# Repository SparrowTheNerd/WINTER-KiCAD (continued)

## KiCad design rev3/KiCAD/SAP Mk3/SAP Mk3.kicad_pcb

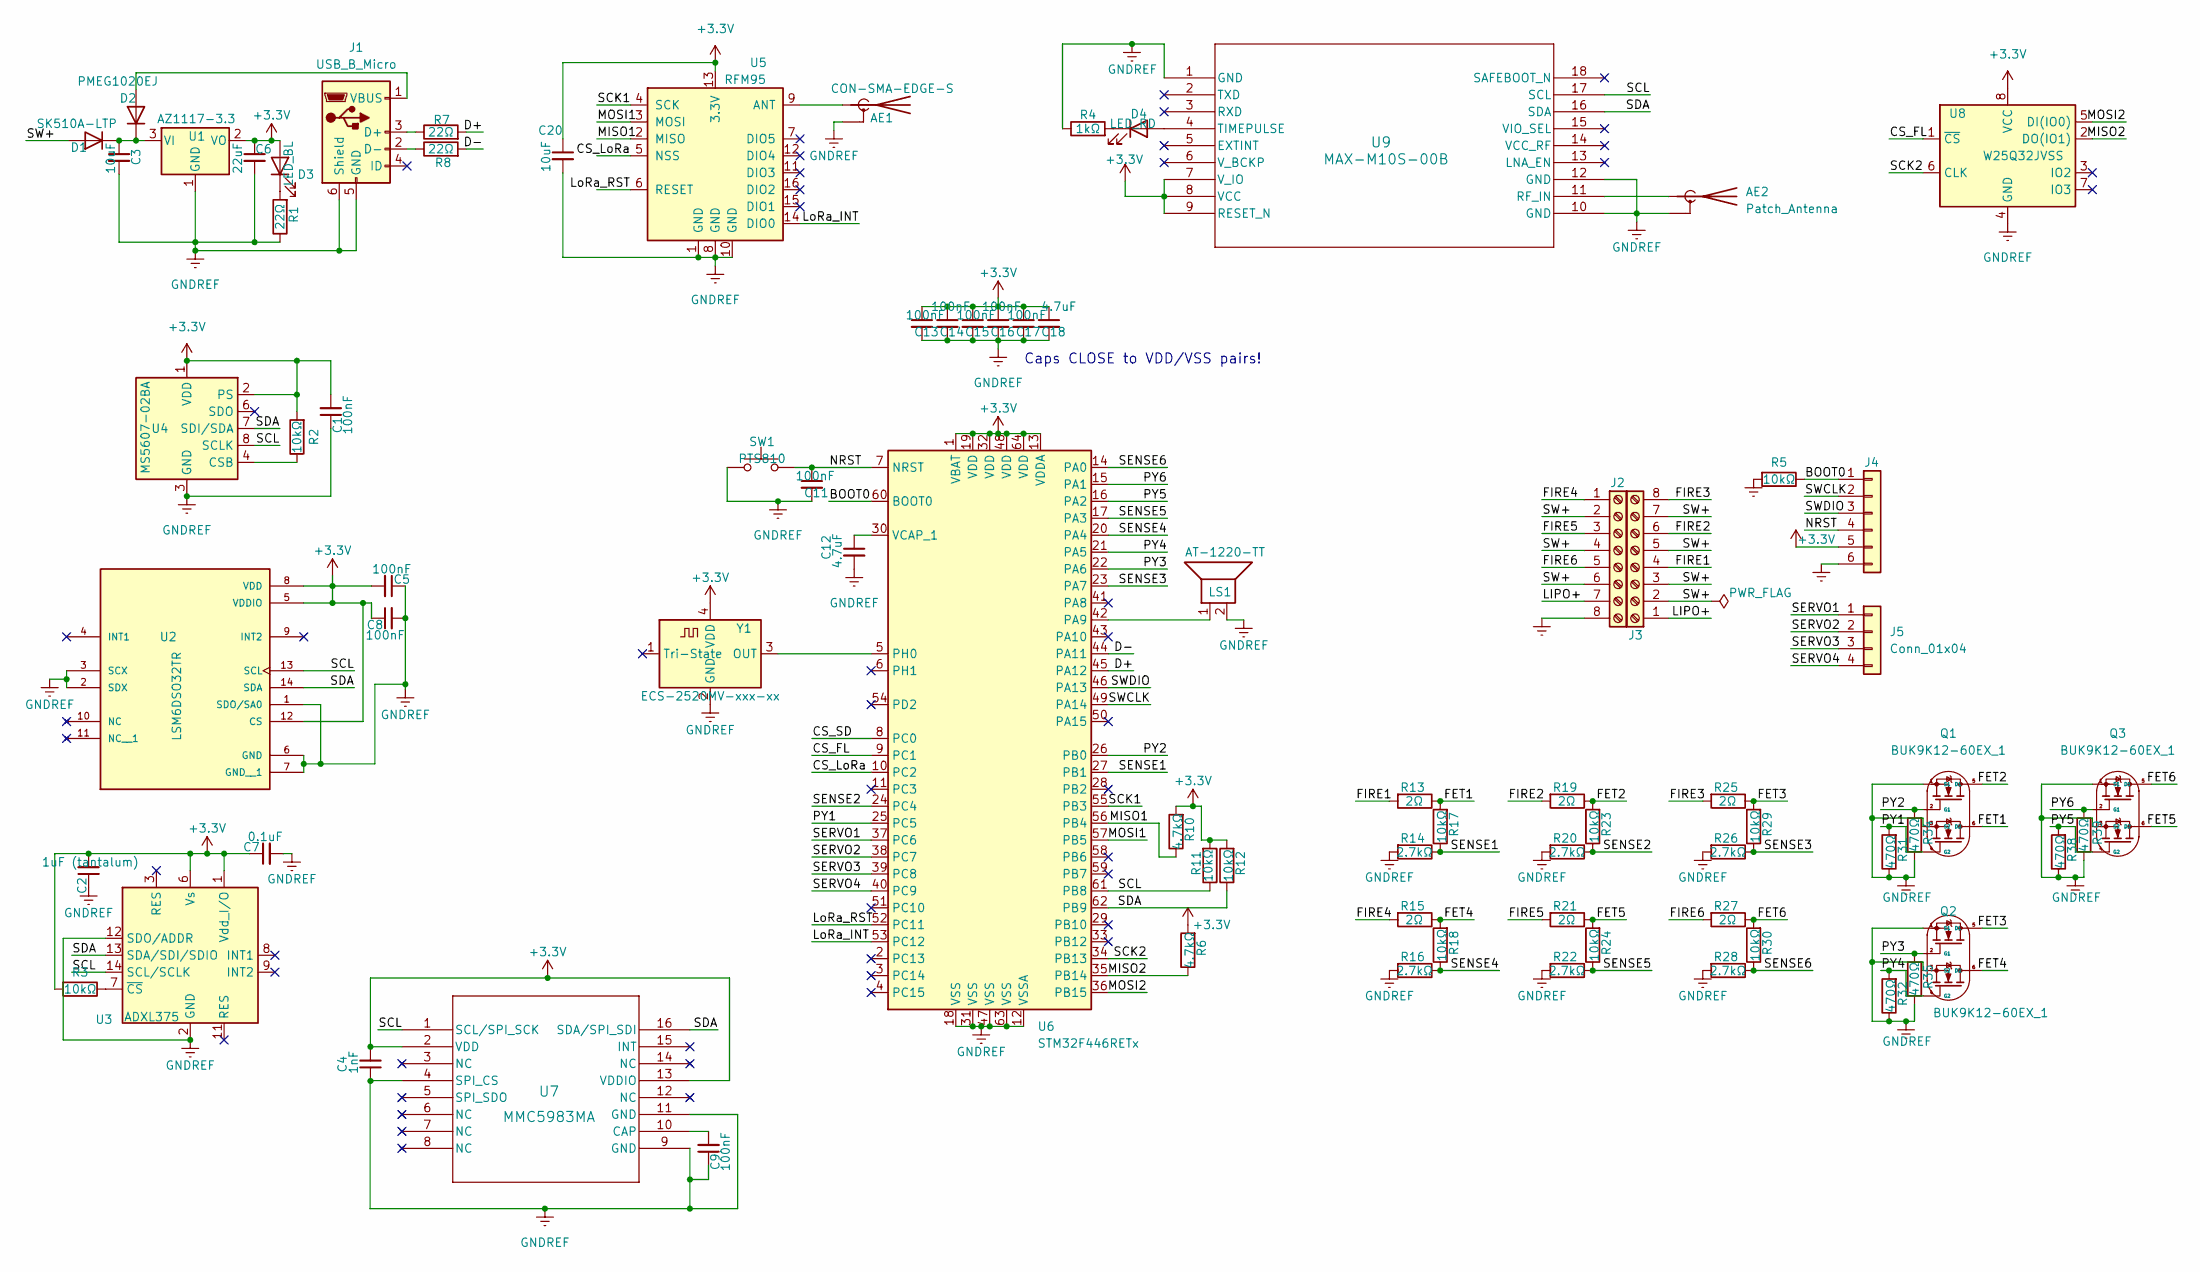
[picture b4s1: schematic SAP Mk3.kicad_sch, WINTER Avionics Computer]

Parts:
AE1: CON-SMA-EDGE-S; U.FL_Molex_MCRF_73412-0110_Vertical
AE2: Patch_Antenna; TAOGLAS SGGP.12.4.A.02
C1, C5, C8, C9, C11, C13, C14, C15, C16, C17: 100nF; C_0603_1608Metric
C2: 1uF (tantalum); C_0603_1608Metric
C3, C20: 10uF; C_0603_1608Metric
C4: 1nF; C_0603_1608Metric
C6: 22uF; C_0603_1608Metric
C7: 0.1uF; C_0603_1608Metric
C12, C18: 4.7uF; C_0603_1608Metric
D1: SK510A-LTP; D_SMA
D2: PMEG1020EJ; D_SOD-323F
D3: LED_BL; LED_0603_1608Metric
D4: LED_RD; LED_0603_1608Metric
J1: USB_B_Micro; USB_Micro-B_GCT_USB3076-30-A
J2, J3: Screw_Terminal_01x08; TerminalBlock_TE_282834-8_1x08_P2.54mm_Horizontal
J4: Conn_01x06; PinHeader_1x06_P2.54mm_Vertical
J5: Conn_01x04; PinHeader_1x04_P2.54mm_Vertical
LS1: AT-1220-TT; MagneticBuzzer_ProSignal_ABT-410-RC
Q1, Q2, Q3: BUK9K12-60EX_1; LFPAK56D
R1, R7, R8: 22Ω; R_0603_1608Metric
R2, R3, R5, R11, R12, R17, R18, R23, R24, R29, R30: 10kΩ; R_0603_1608Metric
R4: 1kΩ; R_0603_1608Metric
R6, R10: 4.7kΩ; R_0603_1608Metric
R13, R15, R19, R21, R25, R27: 2Ω; R_0603_1608Metric
R14, R16, R20, R22, R26, R28: 2.7kΩ; R_0603_1608Metric
R31, R32, R34, R35, R38, R39: 470Ω; R_0603_1608Metric
SW1: PTS810; SW_SPST_PTS810
U1: AZ1117-3.3; TO-252-3_TabPin2
U2: LSM6DSO32TR; PARTREV 1
U3: ADXL375; LGA-14_3x5mm_P0.8mm_LayoutBorder1x6y
U4: MS5607-02BA; LGA-8_3x5mm_P1.25mm
U5: RFM95; HOPERF_RFM9XW_SMD
U6: STM32F446RETx; LQFP-64_10x10mm_P0.5mm
U7: MMC5983MA; MMC5983MA_MEM
U8: W25Q32JVSS; SOIC-8_5.23x5.23mm_P1.27mm
U9: MAX-M10S-00B
Y1: ECS-2520MV-xxx-xx; Oscillator_SMD_ECS_2520MV-xxx-xx-4Pin_2.5x2.0mm

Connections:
+3V3: C1.2, C2.2, C4.2, C5.2, C6.1, C7.1, C8.1, C13.1, C14.1, C15.1, C16.1, C17.1, C18.1, C20.1, D3.2 (A), J4.5, R2.2, R3.2, R6.2, R10.2, R11.2, R12.2, U1.2 (VO), U2.5 (VDDIO), U2.8 (VDD), U2.12 (CS), U3.1 (Vdd_I/O), U3.6 (Vs), U4.1 (VDD), U4.2 (PS), U5.13 (3.3V), U6.1 (VBAT), U6.13 (VDDA), U6.19 (VDD), U6.32 (VDD), U6.48 (VDD), U6.64 (VDD), U7.2 (VDD), U7.13 (VDDIO), U8.8 (VCC), U9.7 (V_IO), U9.8 (VCC), U9.9 (RESET_N), Y1.4 (VDD)
/BOOT0: J4.1, R5.1, U6.60 (BOOT0)
/CS_FL: U6.9 (PC1), U8.1 (~CS)
/CS_LoRa: U5.5 (NSS), U6.10 (PC2)
/CS_SD: U6.8 (PC0)
/D+: R7.2, U6.45 (PA12)
/D-: R8.2, U6.44 (PA11)
/FET1: Q1.6 (D2), R13.1, R17.2
/FET2: Q1.5 (D1), R19.1, R23.2
/FET3: Q2.5 (D1), R25.1, R29.2
/FET4: Q2.6 (D2), R15.1, R18.2
/FET5: Q3.6 (D2), R21.1, R24.2
/FET6: Q3.5 (D1), R27.1, R30.2
/FIRE1: J3.4, R13.2
/FIRE2: J3.6, R19.2
/FIRE3: J3.8, R25.2
/FIRE4: J2.1, R15.2
/FIRE5: J2.3, R21.2
/FIRE6: J2.5, R27.2
/LIPO+: J2.7, J3.1
/LoRa_INT: U5.14 (DIO0), U6.53 (PC12)
/LoRa_RST: U5.6 (RESET), U6.52 (PC11)
/MISO1: R10.1, U5.2 (MISO), U6.56 (PB4)
/MISO2: R6.1, U6.35 (PB14), U8.2 (DO(IO1))
/MOSI1: U5.3 (MOSI), U6.57 (PB5)
/MOSI2: U6.36 (PB15), U8.5 (DI(IO0))
/NRST: C11.1, J4.4, SW1.2 (B), U6.7 (NRST)
/PY1: Q1.4 (G2), R31.2, U6.25 (PC5)
/PY2: Q1.2 (G1), R34.2, U6.26 (PB0)
/PY3: Q2.2 (G1), R35.2, U6.22 (PA6)
/PY4: Q2.4 (G2), R32.2, U6.21 (PA5)
/PY5: Q3.4 (G2), R38.2, U6.16 (PA2)
/PY6: Q3.2 (G1), R39.2, U6.15 (PA1)
/SCK1: U5.4 (SCK), U6.55 (PB3)
/SCK2: U6.34 (PB13), U8.6 (CLK)
/SCL: R11.1, U2.13 (SCL), U3.14 (SCL/SCLK), U4.8 (SCLK), U6.61 (PB8), U7.1 (SCL/SPI_SCK), U9.17 (SCL)
/SDA: R12.1, U2.14 (SDA), U3.13 (SDA/SDI/SDIO), U4.7 (SDI/SDA), U6.62 (PB9), U7.16 (SDA/SPI_SDI), U9.16 (SDA)
/SENSE1: R14.1, R17.1, U6.27 (PB1)
/SENSE2: R20.1, R23.1, U6.24 (PC4)
/SENSE3: R26.1, R29.1, U6.23 (PA7)
/SENSE4: R16.1, R18.1, U6.20 (PA4)
/SENSE5: R22.1, R24.1, U6.17 (PA3)
/SENSE6: R28.1, R30.1, U6.14 (PA0)
/SERVO1: J5.1, U6.37 (PC6)
/SERVO2: J5.2, U6.38 (PC7)
/SERVO3: J5.3, U6.39 (PC8)
/SERVO4: J5.4, U6.40 (PC9)
/SW+: D1.2 (A), J2.2, J2.4, J2.6, J3.2, J3.3, J3.5, J3.7
/SWCLK: J4.2, U6.49 (PA14)
/SWDIO: J4.3, U6.46 (PA13)
GNDREF: AE1.2 (Shield), AE2.1 (Shield), C1.1, C2.1, C3.2, C4.1, C5.1, C6.2, C7.2, C8.2, C9.1, C11.2, C12.2, C13.2, C14.2, C15.2, C16.2, C17.2, C18.2, C20.2, J1.5 (GND), J1.6 (Shield), J2.8, J4.6, LS1.2, Q1.1 (S1), Q1.3 (S2), Q2.1 (S1), Q2.3 (S2), Q3.1 (S1), Q3.3 (S2), R1.1, R4.1, R5.2, R14.2, R16.2, R20.2, R22.2, R26.2, R28.2, R31.1, R32.1, R34.1, R35.1, R38.1, R39.1, SW1.1 (A), U1.1 (GND), U2.1 (SDO/SA0), U2.2 (SDX), U2.3 (SCX), U2.6 (GND), U2.7 (GND__1), U3.2 (GND), U3.4 (GND), U3.5 (GND), U3.12 (SDO/ADDR), U4.3 (GND), U5.1 (GND), U5.8 (GND), U5.10 (GND), U6.12 (VSSA), U6.18 (VSS), U6.31 (VSS), U6.47 (VSS), U6.63 (VSS), U7.4 (SPI_CS), U7.9 (GND), U7.11 (GND), U8.4 (GND), U9.1 (GND), U9.10 (GND), U9.12 (GND), Y1.2 (GND)
unnamed: AE1.1 (A), U5.9 (ANT)
unnamed: AE2.2 (A), U9.11 (RF_IN)
unnamed: C3.1, D1.1 (K), D2.1 (K), U1.3 (VI)
unnamed: D2.2 (A), J1.1 (VBUS)
unnamed: D3.1 (K), R1.2
unnamed: D4.2 (A), U9.4 (TIMEPULSE)
unnamed: D4.1 (K), R4.2
unnamed: J1.3 (D+), R7.1
unnamed: J1.2 (D-), R8.1
unnamed: R2.1, U4.4 (CSB), U4.5 (CSB)
unnamed: R3.1, U3.7 (~CS)
unnamed: LS1.1, U6.42 (PA9)
unnamed: U6.5 (PH0), Y1.3 (OUT)
unnamed: C12.1, U6.30 (VCAP_1)
unnamed: C9.2, U7.10 (CAP)

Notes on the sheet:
Caps CLOSE to VDD/VSS pairs!

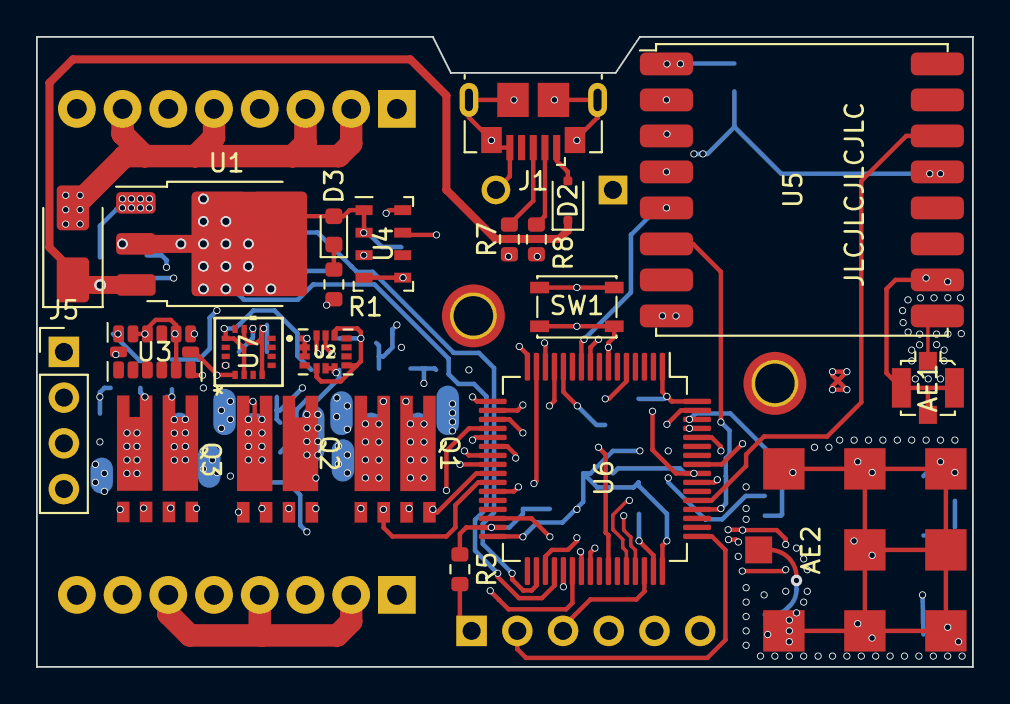
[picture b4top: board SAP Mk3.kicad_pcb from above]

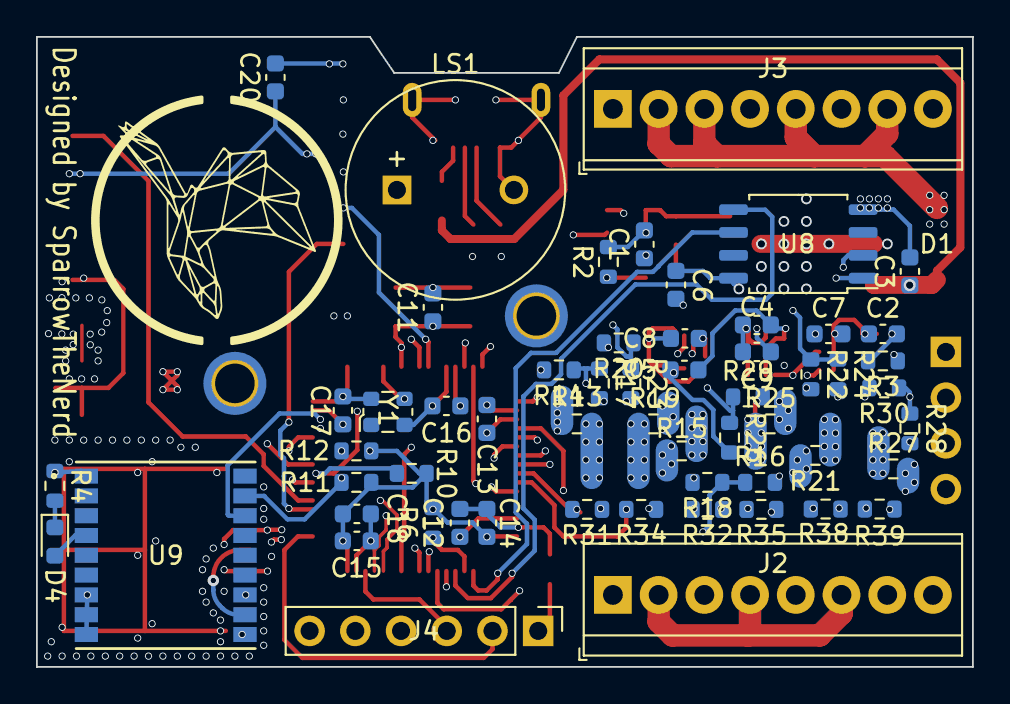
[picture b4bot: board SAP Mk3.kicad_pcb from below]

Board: 8 copper layers, 52.0 x 35.0 mm, 79 parts (57 on the bottom side), 65 nets.

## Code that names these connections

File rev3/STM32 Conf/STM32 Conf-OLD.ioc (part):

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Mcu.Name=STM32H725RGVx
Mcu.Package=VFQFPN68
Mcu.UserName=STM32H725RGVx
PA0.GPIOParameters=GPIO_Label
PA0.GPIO_Label=SENS6
PA0.Mode=IN16-Single-Ended
PA0.Signal=ADC1_INP16
PA1.GPIOParameters=GPIO_PuPd,GPIO_Label
PA1.GPIO_Label=PY6
PA1.GPIO_PuPd=GPIO_NOPULL
PA1.Signal=GPIO_Output
PA10.GPIOParameters=GPIO_Label
PA10.GPIO_Label=LoRa PA EN
PA10.Signal=GPIO_Output
PA11.Mode=Device_Only_FS
PA11.Signal=USB_OTG_HS_DM
PA12.Mode=Device_Only_FS
PA12.Signal=USB_OTG_HS_DP
PA13(JTMS/SWDIO).GPIOParameters=GPIO_Label
PA13(JTMS/SWDIO).GPIO_Label=SWDIO
PA13(JTMS/SWDIO).Mode=Serial_Wire
PA13(JTMS/SWDIO).Signal=DEBUG_JTMS-SWDIO
PA14(JTCK/SWCLK).GPIOParameters=GPIO_Label
PA14(JTCK/SWCLK).GPIO_Label=SWCLK
PA14(JTCK/SWCLK).Mode=Serial_Wire
PA14(JTCK/SWCLK).Signal=DEBUG_JTCK-SWCLK
PA15(JTDI).Signal=S_TIM2_CH1_ETR
PA2.GPIOParameters=GPIO_PuPd,GPIO_Label
PA2.GPIO_Label=PY5
PA2.GPIO_PuPd=GPIO_NOPULL
PA2.Signal=GPIO_Output
PA3.GPIOParameters=GPIO_Label
PA3.GPIO_Label=SENS5
PA3.Signal=ADCx_INP15
PA4.GPIOParameters=GPIO_Label
PA4.GPIO_Label=SENS4
PA4.Signal=ADCx_INP18
PA5.GPIOParameters=GPIO_PuPd,GPIO_Label
PA5.GPIO_Label=PY4
PA5.GPIO_PuPd=GPIO_NOPULL
PA5.Signal=GPIO_Output
PA6.GPIOParameters=GPIO_PuPd,GPIO_Label
PA6.GPIO_Label=PY3
PA6.GPIO_PuPd=GPIO_NOPULL
PA6.Signal=GPIO_Output
PA7.GPIOParameters=GPIO_Label
PA7.GPIO_Label=SENS3
PA7.Signal=ADCx_INP7
PA8.Mode=I2C
PA8.Signal=I2C3_SCL
PB0.GPIOParameters=GPIO_PuPd,GPIO_Label
PB0.GPIO_Label=PY1
PB0.GPIO_PuPd=GPIO_NOPULL
PB0.Signal=GPIO_Output
PB1.GPIOParameters=GPIO_Label
PB1.GPIO_Label=SENS1
PB1.Signal=ADCx_INP5
PB10.GPIOParameters=GPIO_Label
PB10.GPIO_Label=LoRa BUSY
PB10.Signal=GPIO_Input
PB13.GPIOParameters=GPIO_Label
PB13.GPIO_Label=LoRa SCK
PB13.Mode=Full_Duplex_Master
PB13.Signal=SPI2_SCK
PB14.GPIOParameters=GPIO_Label
PB14.GPIO_Label=LoRa MISO
PB14.Mode=Full_Duplex_Master
PB14.Signal=SPI2_MISO
PB15.GPIOParameters=GPIO_Label
PB15.GPIO_Label=LoRa MOSI
PB15.Mode=Full_Duplex_Master
PB15.Signal=SPI2_MOSI
PB3(JTDO/TRACESWO).GPIOParameters=GPIO_Label
PB3(JTDO/TRACESWO).GPIO_Label=SD SCK
PB3(JTDO/TRACESWO).Mode=Full_Duplex_Master
PB3(JTDO/TRACESWO).Signal=SPI1_SCK
PB4(NJTRST).GPIOParameters=GPIO_Label
PB4(NJTRST).GPIO_Label=SD MISO
PB4(NJTRST).Mode=Full_Duplex_Master
PB4(NJTRST).Signal=SPI1_MISO
PB5.GPIOParameters=GPIO_Label
PB5.GPIO_Label=SD MOSI
PB5.Mode=Full_Duplex_Master
PB5.Signal=SPI1_MOSI
PB6.GPIOParameters=GPIO_Label
PB6.GPIO_Label=SERVO4
PB6.Signal=S_TIM4_CH1
PB7.GPIOParameters=GPIO_Label
PB7.GPIO_Label=SERVO3
PB7.Signal=S_TIM4_CH2
PB8.GPIOParameters=GPIO_Label
PB8.GPIO_Label=SERVO2
PB8.Signal=S_TIM4_CH3
PB9.GPIOParameters=GPIO_Label
PB9.GPIO_Label=SERVO1
PB9.Signal=S_TIM4_CH4
PC0.GPIOParameters=GPIO_Label
PC0.GPIO_Label=LIPO-VOLT
PC0.Signal=ADCx_INP10
PC10.GPIOParameters=GPIO_Label
PC10.GPIO_Label=IMU_INT
PC10.Signal=GPXTI10
PC11.GPIOParameters=GPIO_Label
PC11.GPIO_Label=HIGHG_INT
PC11.Signal=GPXTI11
PC12.GPIOParameters=GPIO_Label
PC12.GPIO_Label=MAG_INT
PC12.Signal=GPXTI12
PC4.GPIOParameters=GPIO_Label
PC4.GPIO_Label=SENS2
PC4.Signal=ADCx_INP4
PC5.GPIOParameters=GPIO_PuPd,GPIO_Label
PC5.GPIO_Label=PY2
PC5.GPIO_PuPd=GPIO_NOPULL
PC5.Signal=GPIO_Output
PC6.GPIOParameters=GPIO_PuPd,GPIO_Label
PC6.GPIO_Label=LoRa CS
PC6.GPIO_PuPd=GPIO_NOPULL
PC6.Signal=GPIO_Output
PC7.GPIOParameters=GPIO_Label
PC7.GPIO_Label=LoRa RST
PC7.Signal=GPIO_Output
PC9.Mode=I2C
PC9.Signal=I2C3_SDA
PD2.GPIOParameters=GPIO_PuPd,GPIO_Label
PD2.GPIO_Label=SD CS
PD2.GPIO_PuPd=GPIO_NOPULL
PD2.Signal=GPIO_Output
PH0-OSC_IN.Mode=HSE-External-Clock-Source
PH0-OSC_IN.Signal=RCC_OSC_IN
RCC.HSE_VALUE=24000000
RCC.SYSCLKFreq_VALUE=240000000
RCC.SYSCLKSource=RCC_SYSCLKSOURCE_PLLCLK
board=custom

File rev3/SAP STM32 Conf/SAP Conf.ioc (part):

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Mcu.Name=STM32F446R(C-E)Tx
Mcu.Package=LQFP64
Mcu.UserName=STM32F446RETx
PA0-WKUP.Signal=ADCx_IN0
PA1.GPIOParameters=GPIO_Label
PA1.GPIO_Label=PY1
PA1.Signal=GPIO_Output
PA11.Mode=Device_Only
PA11.Signal=USB_OTG_FS_DM
PA12.Mode=Device_Only
PA12.Signal=USB_OTG_FS_DP
PA13.Mode=Serial_Wire
PA13.Signal=SYS_JTMS-SWDIO
PA14.Mode=Serial_Wire
PA14.Signal=SYS_JTCK-SWCLK
PA2.GPIOParameters=GPIO_Label
PA2.GPIO_Label=PY2
PA2.Signal=GPIO_Output
PA3.Signal=ADCx_IN3
PA4.Signal=ADCx_IN4
PA5.GPIOParameters=GPIO_Label
PA5.GPIO_Label=PY3
PA5.Signal=GPIO_Output
PA6.GPIOParameters=GPIO_Label
PA6.GPIO_Label=PY4
PA6.Signal=GPIO_Output
PA7.Signal=ADCx_IN7
PA9.Signal=GPIO_Output
PB0.GPIOParameters=GPIO_Label
PB0.GPIO_Label=PY6
PB0.Signal=GPIO_Output
PB1.Signal=ADCx_IN9
PB13.Mode=Full_Duplex_Master
PB13.Signal=SPI2_SCK
PB14.Mode=Full_Duplex_Master
PB14.Signal=SPI2_MISO
PB15.Mode=Full_Duplex_Master
PB15.Signal=SPI2_MOSI
PB3.Mode=Full_Duplex_Master
PB3.Signal=SPI1_SCK
PB4.Mode=Full_Duplex_Master
PB4.Signal=SPI1_MISO
PB5.Mode=Full_Duplex_Master
PB5.Signal=SPI1_MOSI
PB8.Mode=I2C
PB8.Signal=I2C1_SCL
PB9.Mode=I2C
PB9.Signal=I2C1_SDA
PC1.Signal=GPIO_Output
PC11.Signal=GPIO_Output
PC12.Signal=GPXTI12
PC15-OSC32_OUT.Signal=GPIO_Input
PC2.Signal=GPIO_Output
PC4.Signal=ADCx_IN14
PC5.GPIOParameters=GPIO_Label
PC5.GPIO_Label=PY5
PC5.Signal=GPIO_Output
PC6.Signal=S_TIM3_CH1
PC7.Signal=S_TIM3_CH2
PC8.Signal=S_TIM3_CH3
PC9.Signal=S_TIM3_CH4
PH0-OSC_IN.Mode=HSE-External-Oscillator
PH0-OSC_IN.Signal=RCC_OSC_IN
PH1-OSC_OUT.Mode=HSE-External-Oscillator
PH1-OSC_OUT.Signal=RCC_OSC_OUT
RCC.HSE_VALUE=25000000
RCC.SYSCLKFreq_VALUE=128000000
RCC.SYSCLKSource=RCC_SYSCLKSOURCE_PLLRCLK
board=custom

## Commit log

2025-08-28 Updated file naming and keep only latest board version in master
2025-08-28 create legacy branch with old board files
2025-08-28 Create legacy branch for revision 3.3 board files
2025-08-28 Fix footprints and update rev number
2025-08-28 Added previously missing V_CORE 1.35V regulator
2025-08-28 Some layout tweaks
2025-09-04 Started new layout and updated power circuitry
2025-11-05 updated power delivery and component choices. v4 now ready
2025-11-26 Fixed power distribution and made small improvements. Updated revision number
